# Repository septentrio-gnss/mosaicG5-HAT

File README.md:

# mosaicG5 HAT

|mosaicG5 HAT| Open-source GNSS HAT for Raspberry Pi|
|------|-------|
|Author|  [laekaz](https://github.com/laekaz)|
|Maintainer| [Septentrio gnss github user](githubuser@septentrio.com)|
|external website| https://github.com/septentrio-gnss/mosaicG5-HAT  |
|License| [CC BY-SA 4.0](https://creativecommons.org/licenses/by-sa/4.0/) and [open-source](https://www.oshwa.org/definition/) |

## Table of Content

* [Introduction to mosaicG5 HAT](#introduction-to-mosaicg5-hat)
  * [What is the mosaicG5 HAT?](#what-is-the-mosaicg5-hat)
  * [A HAT for Raspberry Pi?](#a-hat-for-raspberry-pi)
    * [Robust Mechanical Design](#robust-mechanical-design)
   * [Produce yourself?](#produce-yourself)
    * [Do I need to source special components for producing this board?](#do-i-need-to-source-special-components-for-producing-this-board)
  * [What is a mosaic-G5 module?](#what-is-a-mosaic-g5-module)
    * [Other mosaic-G5 versions](#other-mosaic-g5-versions)
  * [Who is Septentrio?](#who-is-septentrio)
  * [Deliverables](#deliverables)
  * [Is the project open-source?](#is-the-project-open-source)

* [Disclaimer](#disclaimer)

## Introduction to mosaicG5 HAT

### What is the mosaicG5 HAT?
The mosaicG5 HAT is an add-on board that brings high-precision GNSS (GPS) which integrates [mosaic-G5](https://www.septentrio.com/en/products/gnss-receivers/gnss-receiver-modules) Septentrio's GNSS module with basic communications, allowing the system to receive signals from multiple GNSS constellations, such as GPS, Galileo, GLONASS, and BeiDo. 
The goal of the design is to allow easy hardware prototyping and integration of the mosaic-G5 taking advantage of the computer ecosystem provided by the Raspberry pi environment.

The board can also operate as a standalone device when powered through its USB connector or external power input pins.

### Hardware Versions

The mosaicG5 HAT is available in multiple hardware revisions. The latest revision, **V2**, introduces hardware improvements while maintaining compatibility with the software used with V1.

| Version | Description | Software compatibility |
|--------|--------------|------------------------|
| **V1** | Initial production/reference design | Compatible |
| **V2** | Hardware revision with improved hardware design | Compatible |

For detailed information about the changes, advantages, disadvantages, and design decisions of V2, see the [mosaicG5 HAT V2 Hardware Revision](Documentation/mosaicG5%20HAT%20V2%20Hardware%20Revision.md) documentation.

### A HAT for Raspberry Pi?
HAT stands for *Hardware Attached on Top*. It is a type of add-on board specifically designed to sit on top of a Raspberry Pi and connect directly to its 40-pin GPIO header. HATs follow certain standards so they fit neatly, communicate properly, and are powered safely from the Pi.

#### Robust Mechanical Design

Four dedicated mounting holes provide a secure and rigid connection between the Raspberry Pi and the add-on board.

### Produce yourself?
You can use the design files, Bill of Materials from this project and contact your manufacturing company for production. In this project we used JLCPCB for producing the PCB and assembling it. We used JLCPCB because of its competitive pricing and component availability.

##### Do I need to source special components for producing this board?

Yes, Some components are not available through JLCPCB's standard parts library and must be supplied separately. however, if you are assembling the PCB by yourself, all components are available on DigiKey and clearly listed in the project's Bill of Materials. The mosaic GNSS module can be obtained from Digikey or directly from Septentrio. For larger production volumes, we recommend contacting the Septentrio sales team directly at [Septentrio Contact Page](https://www.septentrio.com/en/contact/ask-question)

### What is a mosaic-G5 module?
The mosaic-G5 is a compact GNSS receiver from Septentrio, engineered for high reliability and precise positioning. It integrates the latest multi-band, multi-constellation GNSS technology, providing accurate positions while minimizing power consumption. The receiver can access signals from all major GNSS constellations, including GPS, Galileo, GLONASS, and BeiDou.

#### Other mosaic-G5 versions
Different versions of the mosaic-G5 are available to suit various applications, as summarized below:

| Features     | [mosaic-G5 P1](https://www.septentrio.com/en/products/gnss-receivers/gnss-receiver-modules/mosaic-g5-p1) | [mosaic-G5 P3](https://www.septentrio.com/en/products/gnss-receivers/gnss-receiver-modules/mosaic-G5-P3) | [mosaic-G5 P3H](https://www.septentrio.com/en/products/gnss-receivers/gnss-receiver-modules/mosaic-G5-P3H) |[mosaic-G5 P6](https://www.septentrio.com/en/products/gnss-receivers/gnss-receiver-modules/mosaic-G5-P6) | [mosaic-G5 P8](https://www.septentrio.com/en/products/gnss-receivers/gnss-receiver-modules/mosaic-g5-p8) |
|--------------|--------------|--------------|---------------|---------------|---------------|
| Functionality|High-precision positioning   |High-precision positioning |Positioning + Heading|Positioning + Heading | Positioning + Heading|
| Use case     |Robotics (e.g robotic mowers), GIS devices |UAV, Commercial mowers, Industrial Robotics, Survey, Marine navigation | Marine navigation, Machine control, Autonomous vehicles,  Survey | Autonomous vehicles, Marine navigation, Machine control, Survey | High-end autonomous systems, Robotics, Marine navigation, Survey, Machine control |          
| GNSS bands   | Triple-band  | Quad-band    | Quad-band     |Quad-band |Quad-band  |
| RTK support  | Yes          | Yes          | Yes           |Yes       |Yes        |
| Dual antenna |    No        |  No          | Yes           |Yes       |Yes        |
| Heading      |     NO       |   No         | Yes           |Yes       |Yes        |

### Who is Septentrio?

Septentrio is a leading company that designs, manufactures and sells high precision and multi-frequency GPS/GNSS receivers for demanding applications. Septentrio products are used in different industries including automotive, marine, construction, rail, machine control, logistics, precision agriculture, geographic information systems (GIS), Unmanned aerial vehicles (UAVs), surveying, mapping and scientific development. Septentrio’s receivers constantly deliver accurate and precise GNSS positioning scalable to centimetre-level and designed to perform perfectly in challenging environments. 

Septentrio's technology offers high accuracy and reliability thanks to advanced GNSS signal-processing algorithms as well as [Advanced interference Monitoring and Mitigation (AIM+)](https://www.septentrio.com/en/learn-more/advanced-positioning-technology/aim-anti-jamming-protection) This protects your application against jamming (RF interference) and spoofing (malicious attacks).

For more information about Septentrio products go to [**https://www.septentrio.com/**](https://web.septentrio.com/GH-SSN-home).

### Deliverables
This project provides the following deliverables for system integrators and hardware designers developing solutions based on Septentrio's mosaic-G5 modules.

|Files         |Description   |
|--------------|--------------|
|  [mosaicG5_RPi_HAT.kicad_pro](./Kicad/mosaicG5%20HAT/V1/mosaicG5_RPi_HAT.kicad_pro)   |KiCad project |
| [mosaicG5_RPi_HAT.kicad_pcb](./Kicad/mosaicG5%20HAT/V1/mosaicG5_RPi_HAT.kicad_pcb) | KiCad layout |
|  [mosaicG5_RPi_HAT.kicad_sch](./Kicad/mosaicG5%20HAT/V1/mosaicG5_RPi_HAT.kicad_sch)  |KiCad schematic |
| [mosaic-G5.STEP](./Kicad/mosaci-G5/mosaic-G5.STEP)  |mosaic-G5 3D |
|  [LGA54_MOSAIC-MINI_SEP.kicad_mod](./Kicad/mosaci-G5/LGA54_MOSAIC-MINI_SEP.kicad_mod) |mosaic footprint |
|  [MG5_1.step](./Kicad/mosaicG5%20HAT%203D/MG5_1.step)  |mosaicG5 HAT 3D |
|[BOM](./Kicad/mosaicG5%20HAT/V1/BOM.xlsx)    | mosaicG5 HAT Bill of Materials |
### Is the project open-source?
Yes, We made this open-source so you can tinker, adapt, and create. If you are building your own robotics project, a spin-off device, or integrating GNSS into a larger system, this is a great starting point.

Open-source here means:
* All files fully editable
* Freedom to modify, remix, and innovate
* You can sell your version. No -NC limitations
* May require attribution
* Build on our work, push it further, and even make money doing it

More info about licensing can be found here: [CC BY-SA 4.0](https://creativecommons.org/licenses/by-sa/4.0/) and [open-source](https://www.oshwa.org/definition/)

## Disclaimer
This project is **offered as-is**. The main interfaces have been tested, but the design has not been fully checked or approved by the author or Septentrio. You are responsible for how you use it in your own projects. For guidance on working with Septentrio’s GNSS mosaic-G5 modules, we suggest reaching out to Septentrio directly.

Support website: https://www.septentrio.com/en/support
### Documentation Sections

This project provides two main documentation sections:

- **[mosaicG5 HAT User Documentation](Documentation/mosaicG5%20HAT%20User%20Documentation.md)**  
  Contains information for users on how to install, configure, and use the mosaicG5 HAT.

- **[mosaicG5 HAT Design Documentation](Documentation/mosaicG5%20HAT%20Design%20Documentation.md)**  
  Intended for hardware designers who want to understand, customize, or modify the reference design of the mosaicG5 HAT.
- **[mosaicG5 HAT V2 Hardware Revision](Documentation/mosaicG5%20HAT%20V2%20Hardware%20Revision.md)**

  Hardware revision with updated hardware design

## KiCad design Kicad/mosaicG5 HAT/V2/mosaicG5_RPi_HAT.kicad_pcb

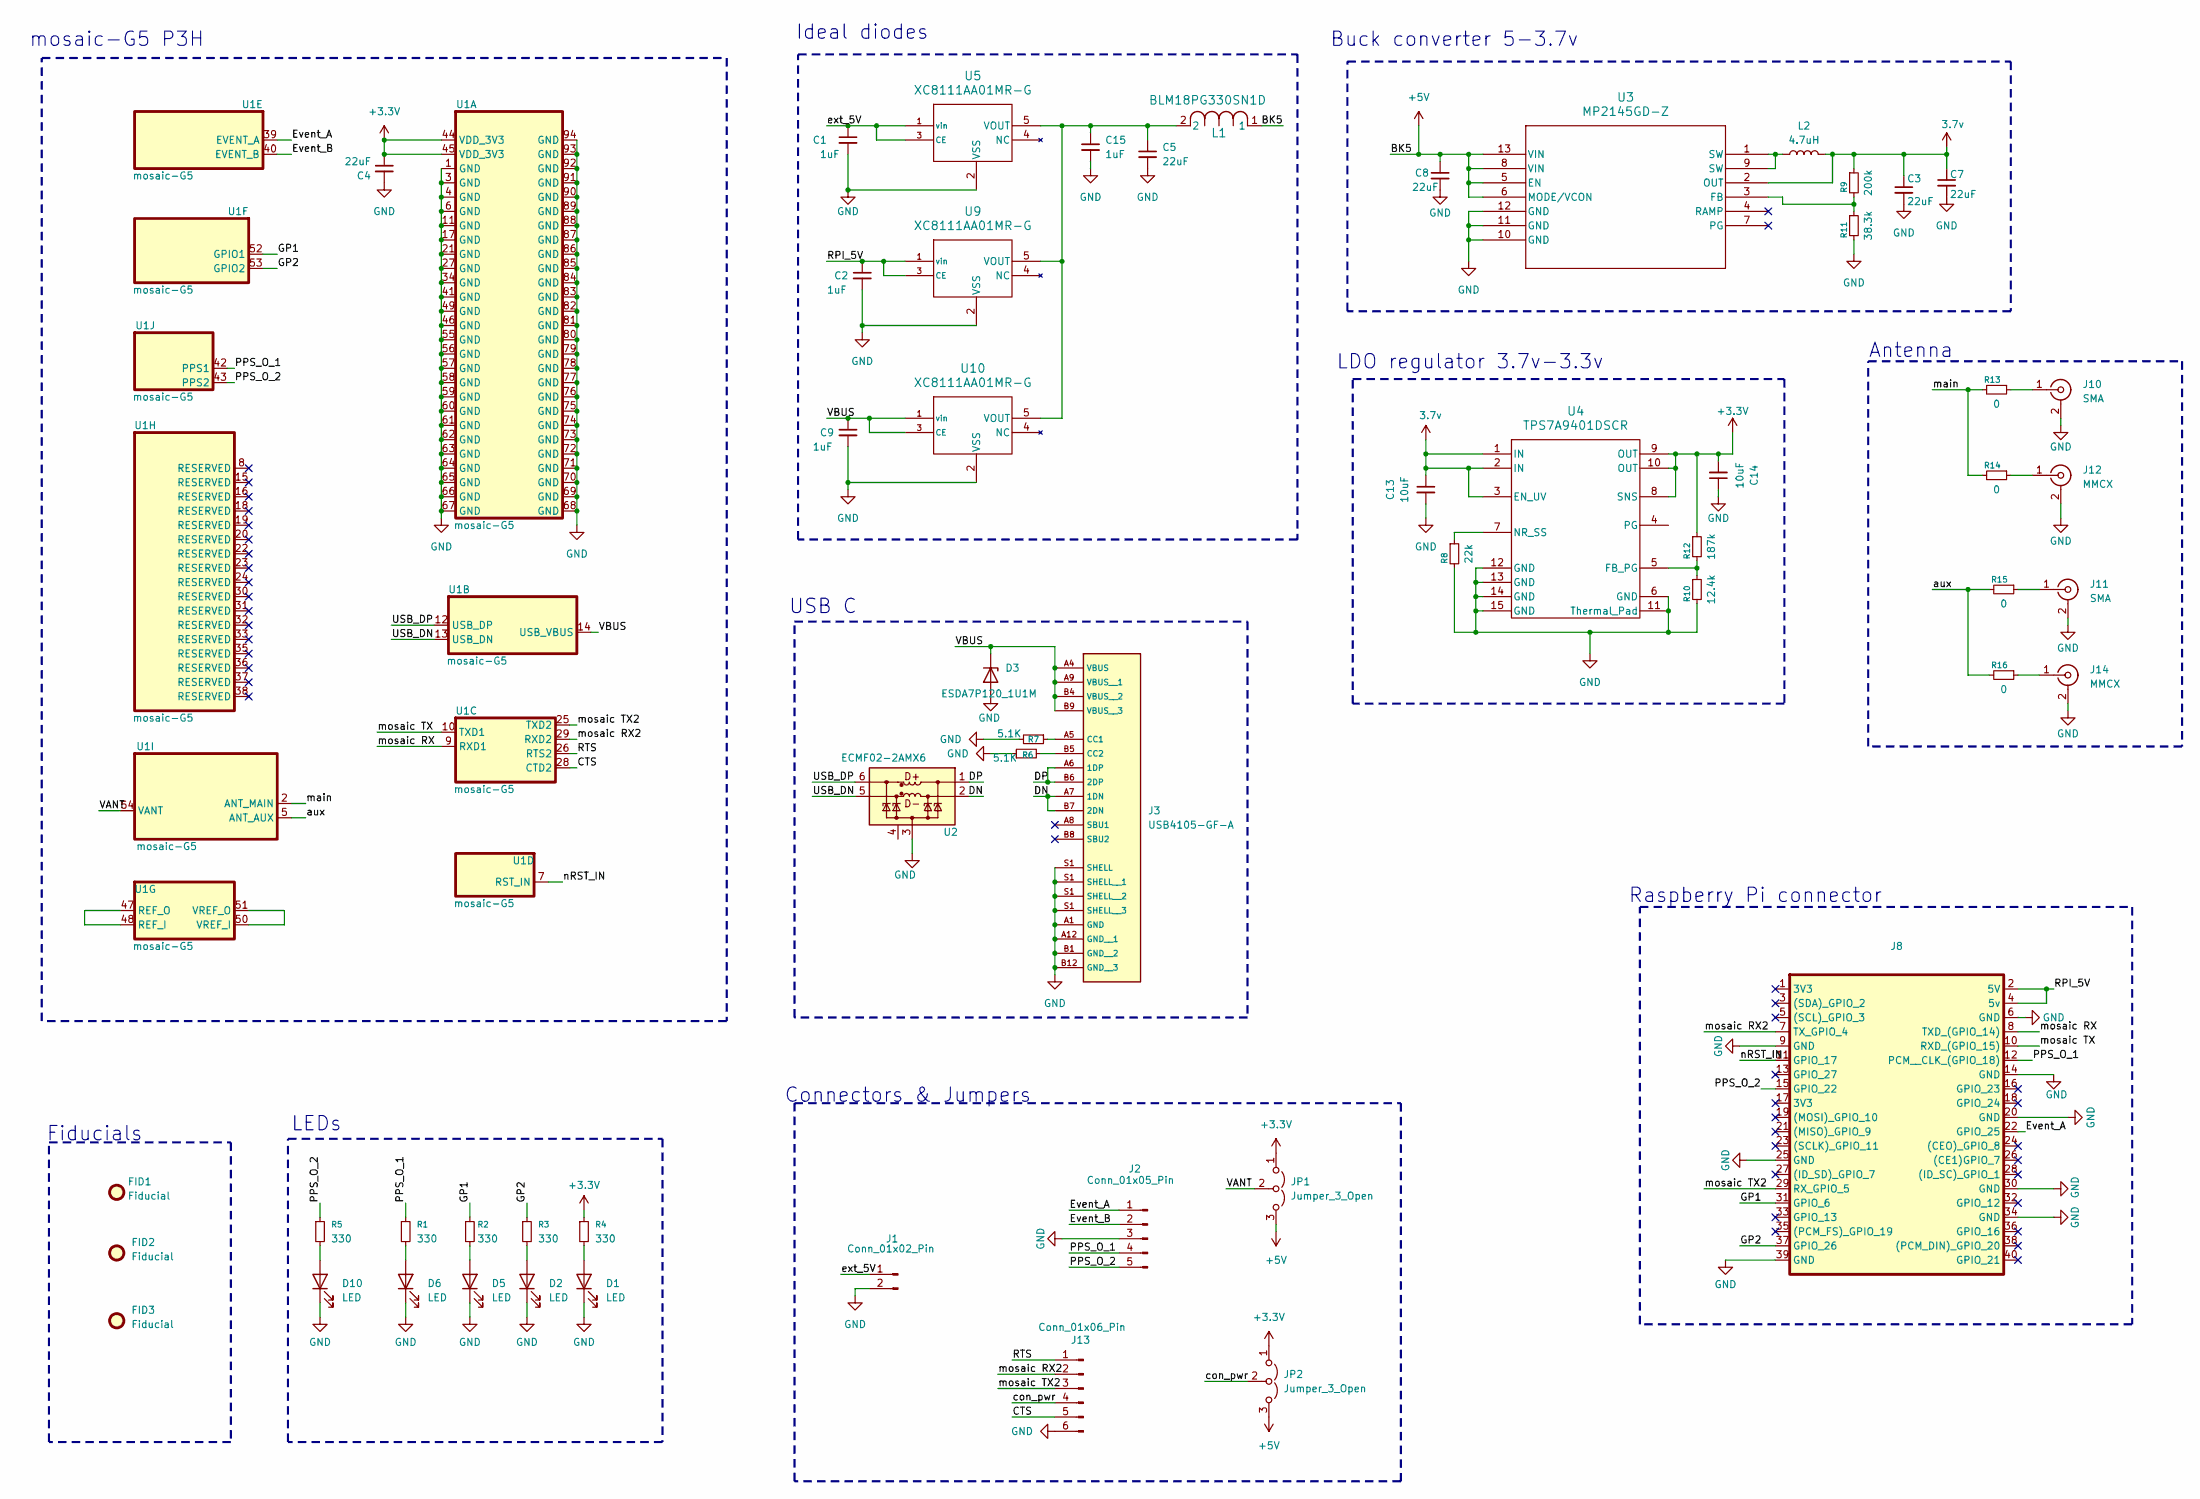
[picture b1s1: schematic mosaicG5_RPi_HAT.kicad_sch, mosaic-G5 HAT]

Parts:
C1, C2, C9, C15: 1uF; C_0603_1608Metric
C3, C5, C7, C8: 22uF; C_0805_2012Metric
C4: 22uF; CAPC1608X90
C13, C14: 10uF; CAPC1608X90
D1, D2, D5, D6, D10: LED; LED_0603_1608Metric
D3: ESDA7P120_1U1M; DIODE_ESDA7P120-1U1M_STM
FID1, FID2, FID3: Fiducial; Fiducial_1mm_Mask2mm
J1: Conn_01x02_Pin; PinHeader_1x02_P2.54mm_Vertical
J2: Conn_01x05_Pin; PinHeader_1x05_P2.54mm_Vertical
J3: USB4105-GF-A; USB_C_Receptacle_GCT_USB4105-xx-A_16P_TopMnt_Horizontal
J8: 2x20 2.54mm pitch
J10, J11: SMA; SMA_Amphenol_132134-16_Vertical
J12, J14: MMCX; SAMTEC_MMCX-J-P-H-ST-TH1
J13: Conn_01x06_Pin; PinHeader_1x06_P2.54mm_Vertical
JP1, JP2: Jumper_3_Open; PinHeader_1x03_P2.00mm_Vertical
L1: BLM18PG330SN1D; IND_BLM18_0603_MUR
L2: 4.7uH; IND_ASPI-4030S-4R7M-T
R1, R2, R3, R4, R5: 330; 0603 (1608metric)
R6, R7: 5.1K; 0603 (1608metric)
R8: 22k; 0603 (1608metric)
R9: 200k; 0603 (1608metric)
R10: 12.4k; 0603 (1608metric)
R11: 38.3k; 0603 (1608metric)
R12: 187k; 0603 (1608metric)
R13, R14, R15, R16: 0; R_0603_1608Metric
U1: mosaic-G5; LGA54_MOSAIC-MINI_SEP
U2: ECMF02-2AMX6; ST_UQFN-6L_1.5x1.7mm_P0.5mm
U3: MP2145GD-Z; QFN-12_MP2145_MNP
U4: TPS7A9401DSCR; DSC0010J-MFG
U5, U9, U10: XC8111AA01MR-G; SOT-25_TOR

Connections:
3.7v: C3.1, C7.1, C13.1, L2.2, R9.1, U3.2 (OUT), U4.1 (IN), U4.2 (IN), U4.3 (EN_UV)
+3.3V: C4.1, C14.2, JP1.1 (A), JP2.1 (A), R4.1, R12.1, U1.44 (VDD_3V3), U1.45 (VDD_3V3), U4.8 (SNS), U4.9 (OUT), U4.10 (OUT)
+5V: C8.1, JP1.3 (B), JP2.3 (B), L1.1, U3.5 (EN), U3.6 (MODE/VCON), U3.8 (VIN), U3.13 (VIN)
/CTS: J13.5, U1.28 (CTD2)
/DN: J3.A7 (1DN), J3.B7 (2DN), U2.2 (D-_in)
/DP: J3.A6 (1DP), J3.B6 (2DP), U2.1 (D+_in)
/Event_A: J2.1, J8.22 (GPIO_25), U1.39 (EVENT_A)
/Event_B: J2.2, U1.40 (EVENT_B)
/GP1: J8.31 (GPIO_6), R2.1, U1.52 (GPIO1)
/GP2: J8.37 (GPIO_26), R3.1, U1.53 (GPIO2)
/PPS_O_1: J2.4, J8.12 (PCM__CLK_(GPIO_18)), R1.1, U1.42 (PPS1)
/PPS_O_2: J2.5, J8.15 (GPIO_22), R5.1, U1.43 (PPS2)
/RPI_5V: C2.1, J8.2 (5V), J8.4 (5v), U9.1 (vin), U9.3 (CE)
/RTS: J13.1, U1.26 (RTS2)
/USB_DN: U1.13 (USB_DN), U2.5 (D-_out)
/USB_DP: U1.12 (USB_DP), U2.6 (D+_out)
/VANT: JP1.2 (C), U1.54 (VANT)
/VBUS: C9.1, D3.1 (K), J3.A4 (VBUS), J3.A9 (VBUS__1), J3.B4 (VBUS__2), J3.B9 (VBUS__3), U1.14 (USB_VBUS), U10.1 (vin), U10.3 (CE)
/aux: R15.2, R16.2, U1.5 (ANT_AUX)
/con_pwr: J13.4, JP2.2 (C)
/ext_5V: C1.1, J1.1, U5.1 (vin), U5.3 (CE)
/main: R13.2, R14.2, U1.2 (ANT_MAIN)
/mosaic RX: J8.8 (TXD_(GPIO_14)), U1.9 (RXD1)
/mosaic RX2: J8.7 (TX_GPIO_4), J13.2, U1.29 (RXD2)
/mosaic TX: J8.10 (RXD_(GPIO_15)), U1.10 (TXD1)
/mosaic TX2: J8.29 (RX_GPIO_5), J13.3, U1.25 (TXD2)
/nRST_IN: J8.11 (GPIO_17), U1.7 (RST_IN)
GND: C1.2, C2.2, C3.2, C4.2, C5.2, C7.2, C8.2, C9.2, C13.2, C14.1, C15.2, D1.1 (K), D2.1 (K), D3.2 (A), D5.1 (K), D6.1 (K), D10.1 (K), J1.2, J2.3, J3.A1 (GND), J3.A12 (GND__1), J3.B1 (GND__2), J3.B12 (GND__3), J3.S1 (SHELL__2), J8.6 (GND), J8.9 (GND), J8.14 (GND), J8.20 (GND), J8.25 (GND), J8.30 (GND), J8.34 (GND), J8.39 (GND), J10.2 (Ext), J11.2 (Ext), J12.2 (Ext), J13.6, J14.2 (Ext), R6.1, R7.2, R8.2, R10.2, R11.2, U1.1 (GND), U1.3 (GND), U1.4 (GND), U1.6 (GND), U1.11 (GND), U1.17 (GND), U1.21 (GND), U1.27 (GND), U1.34 (GND), U1.41 (GND), U1.46 (GND), U1.49 (GND), U1.55 (GND), U1.56 (GND), U1.57 (GND), U1.58 (GND), U1.59 (GND), U1.60 (GND), U1.61 (GND), U1.62 (GND), U1.63 (GND), U1.64 (GND), U1.65 (GND), U1.66 (GND), U1.67 (GND), U1.68 (GND), U1.69 (GND), U1.70 (GND), U1.71 (GND), U1.72 (GND), U1.73 (GND), U1.74 (GND), U1.75 (GND), U1.76 (GND), U1.77 (GND), U1.78 (GND), U1.79 (GND), U1.80 (GND), U1.81 (GND), U1.82 (GND), U1.83 (GND), U1.84 (GND), U1.85 (GND), U1.86 (GND), U1.87 (GND), U1.88 (GND), U1.89 (GND), U1.90 (GND), U1.91 (GND), U1.92 (GND), U1.93 (GND), U1.94 (GND), U2.3 (GND), U3.10 (GND), U3.11 (GND), U3.12 (GND), U4.6 (GND), U4.11 (Thermal_Pad), U4.12 (GND), U4.13 (GND), U4.14 (GND), U4.15 (GND), U5.2 (VSS), U9.2 (VSS), U10.2 (VSS)
unnamed: D1.2 (A), R4.2
unnamed: D2.2 (A), R3.2
unnamed: D5.2 (A), R2.2
unnamed: D6.2 (A), R1.2
unnamed: D10.2 (A), R5.2
unnamed: J3.A5 (CC1), R7.1
unnamed: J3.B5 (CC2), R6.2
unnamed: J10.1 (In), R13.1
unnamed: J11.1 (In), R15.1
unnamed: J12.1 (In), R14.1
unnamed: J14.1 (In), R16.1
unnamed: L2.1, U3.1 (SW), U3.9 (SW)
unnamed: U1.47 (REF_O), U1.48 (REF_I)
unnamed: U1.50 (VREF_I), U1.51 (VREF_O)
unnamed: R9.2, R11.1, U3.3 (FB)
unnamed: R10.1, R12.2, U4.5 (FB_PG)
unnamed: R8.1, U4.7 (NR_SS)
unnamed: C5.1, C15.1, L1.2, U5.5 (VOUT), U9.5 (VOUT), U10.5 (VOUT)

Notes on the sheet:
Fiducials
Connectors & Jumpers
Ideal diodes
mosaic-G5 P3H
Buck converter 5-3.7v
USB C
LDO regulator 3.7v-3.3v
Antenna
Raspberry Pi connector
LEDs

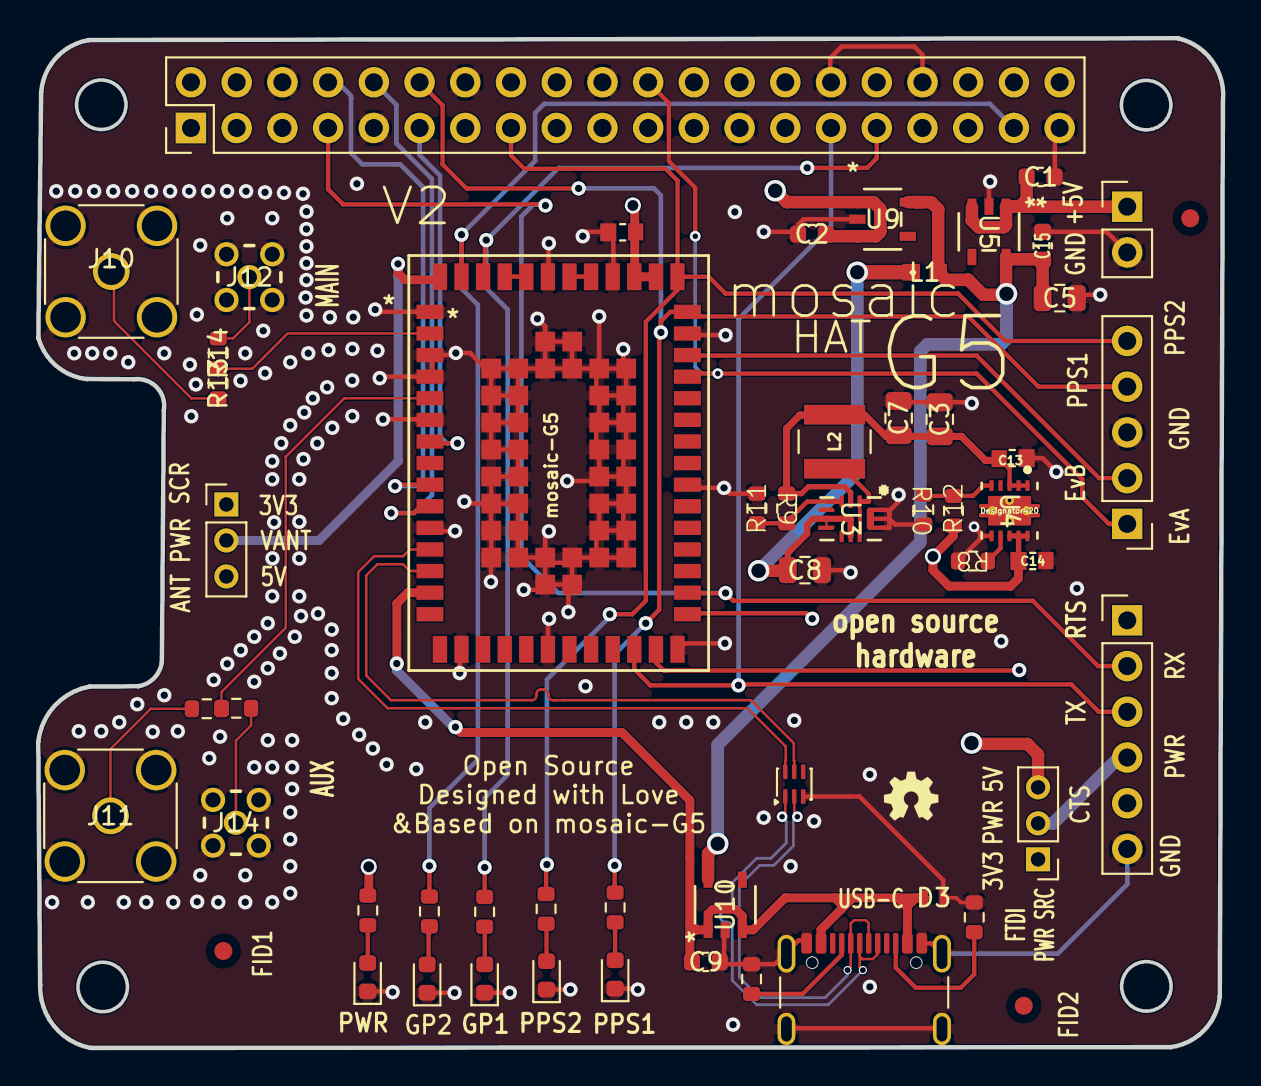
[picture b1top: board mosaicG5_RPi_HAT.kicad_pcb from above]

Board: 4 copper layers, 65.8 x 56.1 mm, 56 parts (0 on the bottom side), 46 nets.

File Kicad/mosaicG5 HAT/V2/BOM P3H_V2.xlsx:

Designator | Value | Package | Part | Quantity
C1 | 1µF | C_0603_1608Metric | C106248 | 1
C13 | 10µF | CAPC1608X90 | C22399626 | 1
C14 | 10µF | CAPC1608X90 | C22399626 | 1
C15 | 1µF | C_0603_1608Metric | C106248 | 1
C2 | 1µF | C_0603_1608Metric | C106248 | 1
C3 | 22µF | C_0805_2012Metric | C23692981 | 1
C4 | 22µF | CAPC1608X90 | C15500 | 1
C5 | 22µF | C_0805_2012Metric | C23692981 | 1
C7 | 22µF | C_0805_2012Metric | C23692981 | 1
C8 | 22µF | C_0805_2012Metric | C23692981 | 1
C9 | 1µF | C_0603_1608Metric | C106248 | 1
D1 | LED | LED_0603_1608Metric | C440514 | 1
D10 | LED | LED_0603_1608Metric | C440514 | 1
D2 | LED | LED_0603_1608Metric | C440514 | 1
D3 | ESDA7P120_1U1M | ESD_ESDA7P120-1U1M | C2969802 | 1
D5 | LED | LED_0603_1608Metric | C440514 | 1
D6 | LED | LED_0603_1608Metric | C440514 | 1
J1 | Conn_01x02_Pin | C2905434 | C2905434 | 1
J10 | Conn_Coaxial SMA | C3174435 | C3174435 | 1
J11 | Conn_Coaxial SMA | C3174435 | C3174435 | 1
J13 | Conn_01x06_Pin | C5444523 | C5444523 | 1
J2 | Conn_01x05_Pin | C6461551 | C6461551 | 1
J3 | USB4105-GF-A | USB_C_Receptacle_GCT_USB4105-xx-A_16P_TopMnt_Horizontal | C3020560 | 1
J8 | 2x20_2.54mm_pitch | C35165 | C35165 | 1
JP1 | Jumper_3_Open | C22438286 | C22438286 | 1
JP2 | Jumper_3_Open | C22438286 | C22438286 | 1
L2 | 4.7µH | IND_ASPI-4030S-4R7M-T | C3224051 | 1
L1 | IND_BLM18_0603_MUR _ 33ohms | BLM18PG330SN1D | C88984
R1 | 330Ω | 0603_(1608metric) | C23138 | 1
R10 | 12.4kΩ | 0603_(1608metric) | C22865 | 1
R11 | 39kΩ | 0603_(1608metric) | C163424 | 1
R12 | 187kΩ | 0603_(1608metric) | C22896 | 1
R13 | 0Ω | 0603_(1608metric) | C177335 | 1
R15 | 0Ω | 0603_(1608metric) | C177335 | 1
R2 | 330Ω | 0603_(1608metric) | C23138 | 1
R3 | 330Ω | 0603_(1608metric) | C23138 | 1
R4 | 330Ω | 0603_(1608metric) | C23138 | 1
R5 | 330Ω | 0603_(1608metric) | C23138 | 1
R6 | 5.1kΩ | 0603_(1608metric) | C123727 | 1
R7 | 5.1kΩ | 0603_(1608metric) | C123727 | 1
R8 | 22kΩ | 0603_(1608metric) | C881373 | 1
R9 | 200kΩ | 0603_(1608metric) | C332260 | 1
U1 | mosaic-G5 P3H | LGA54_MOSAIC-MINI_SEP | LGA54_MOSAIC-MINI_SEP | 1
U10 | XC8111AA01MR-G | SOT-25_TOR | C3235548 | 1
U2 | ECMF02-2AMX6 | ST_UQFN-6L_1.5x1.7mm_P0.5mm | C2651144 | 1
U3 | MP2145GD-Z | QFN-12_MP2145_MNP | C132200 | 1
U4 | TPS7A9401DSCR | DSC0010J-MFG | C5220127 | 1
U5 | XC8111AA01MR-G | SOT-25_TOR | C3235548 | 1
U9 | XC8111AA01MR-G | SOT-25_TOR | C3235548 | 1
